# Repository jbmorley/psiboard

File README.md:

# PsiBoard

Psion Series 5 based bluetooth keyboard.

## BOM

### FFC Connector

https://www.digikey.com/en/products/detail/molex/0524372271/3262899

22 Position FFC, FPC Connector Contacts, Bottom 0.020" (0.50mm) Surface Mount, Right Angle

### Reset Switch

https://www.digikey.com/en/products/detail/panasonic-electronic-components/EVQ-P7A01P/4429447

## Development

### Useful Links

- [ZMK Firmware - List of Keycodes](https://zmk.dev/docs/keymaps/list-of-keycodes)
- [ZMK Firmware - Power Management Configuration](https://zmk.dev/docs/config/power)
- [Pro Micro Pinout](https://learn.sparkfun.com/tutorials/pro-micro--fio-v3-hookup-guide/all)

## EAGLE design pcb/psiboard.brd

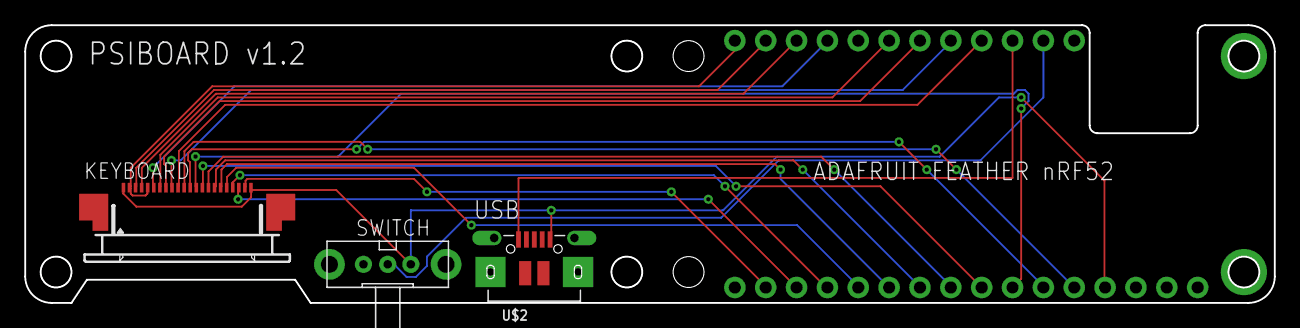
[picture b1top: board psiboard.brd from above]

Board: 2 copper layers, 102.9 x 22.9 mm, 4 parts (1 on the bottom side), 22 nets.

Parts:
FEATHER: FEATHERWING_NODIM; FEATHERWING_DIM
KEYBOARD: 52745-2290
SWITCH: EG1213
U$2: USB_MICRO_PWR; MICROBUILDER_4UCONN_20329

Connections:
2: FEATHER.5, KEYBOARD.11
3: FEATHER.6, KEYBOARD.12
4: FEATHER.7, KEYBOARD.13
5: FEATHER.8, KEYBOARD.14
6: FEATHER.15, KEYBOARD.21
7: FEATHER.23, KEYBOARD.8
8: FEATHER.14, KEYBOARD.20
11: FEATHER.22, KEYBOARD.7
12: FEATHER.11, KEYBOARD.17
13: FEATHER.12, KEYBOARD.18
14: FEATHER.13, KEYBOARD.19
15: FEATHER.24, KEYBOARD.9
16: FEATHER.25, KEYBOARD.10
25: FEATHER.17, KEYBOARD.2, KEYBOARD.5
26: FEATHER.18, KEYBOARD.3
27: FEATHER.19, KEYBOARD.4
28: FEATHER.9, KEYBOARD.15
29: FEATHER.10, KEYBOARD.16
30: FEATHER.20, KEYBOARD.6
EN: FEATHER.27, SWITCH.2
GND: FEATHER.4, KEYBOARD.1, KEYBOARD.22, SWITCH.3, U$2.GND
USB: FEATHER.26, U$2.VBUS

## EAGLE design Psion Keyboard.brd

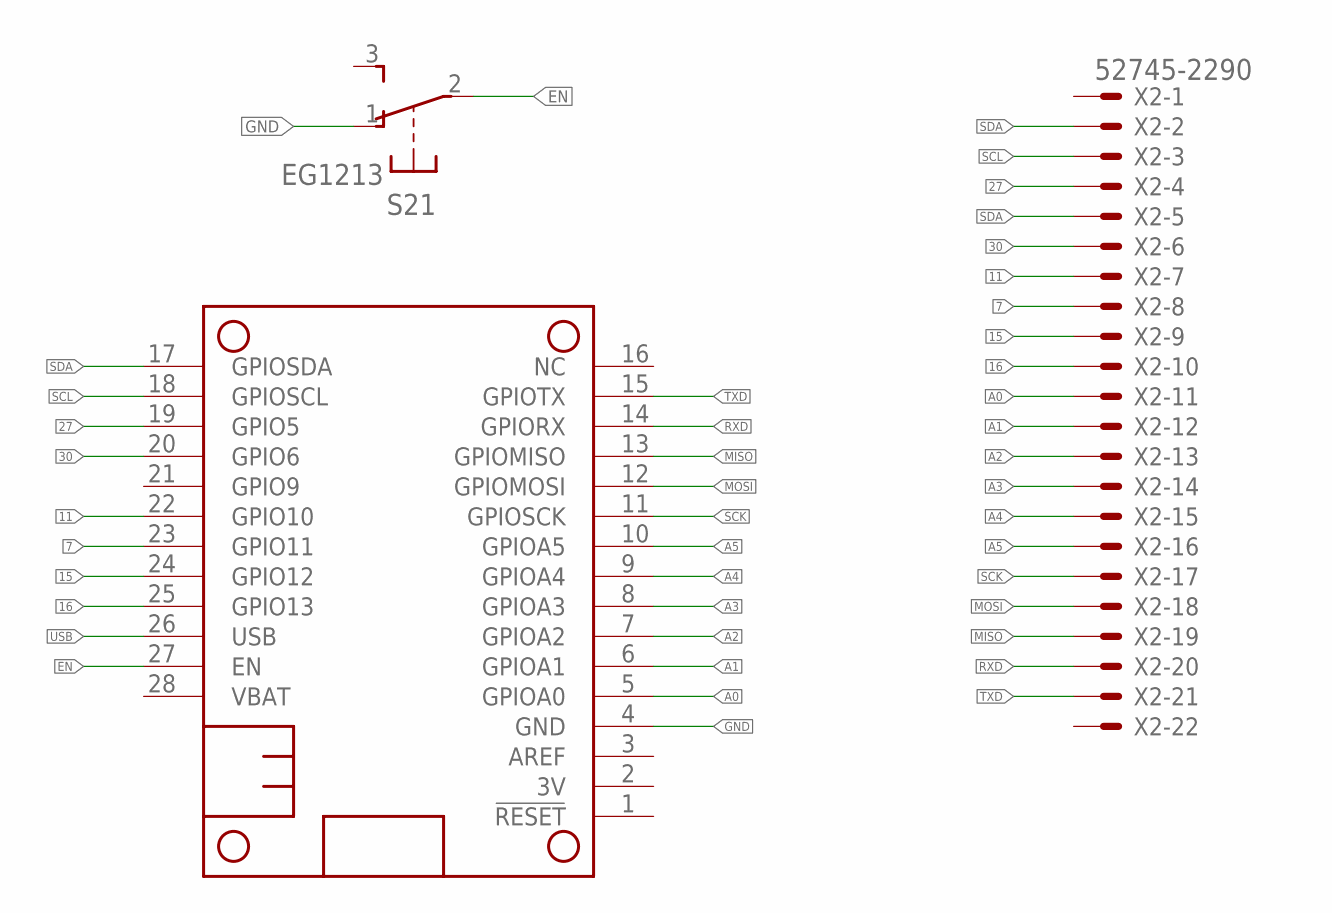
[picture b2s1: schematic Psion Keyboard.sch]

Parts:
MS1: FEATHERWING_NODIM; FEATHERWING_DIM
S2: EG1213
X2: 52745-2290

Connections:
7: MS1.23 (GPIO11), X2.8
11: MS1.22 (GPIO10), X2.7
15: MS1.24 (GPIO12), X2.9
16: MS1.25 (GPIO13), X2.10
27: MS1.19 (GPIO5), X2.4
30: MS1.20 (GPIO6), X2.6
A0: MS1.5 (GPIOA0), X2.11
A1: MS1.6 (GPIOA1), X2.12
A2: MS1.7 (GPIOA2), X2.13
A3: MS1.8 (GPIOA3), X2.14
A4: MS1.9 (GPIOA4), X2.15
A5: MS1.10 (GPIOA5), X2.16
EN: MS1.27 (EN), S2.2
GND: MS1.4 (GND), S2.1 (O)
MISO: MS1.13 (GPIOMISO), X2.19
MOSI: MS1.12 (GPIOMOSI), X2.18
RXD: MS1.14 (GPIORX), X2.20
SCK: MS1.11 (GPIOSCK), X2.17
SCL: MS1.18 (GPIOSCL), X2.3
SDA: MS1.17 (GPIOSDA), X2.2, X2.5
TXD: MS1.15 (GPIOTX), X2.21
USB: MS1.26 (USB)

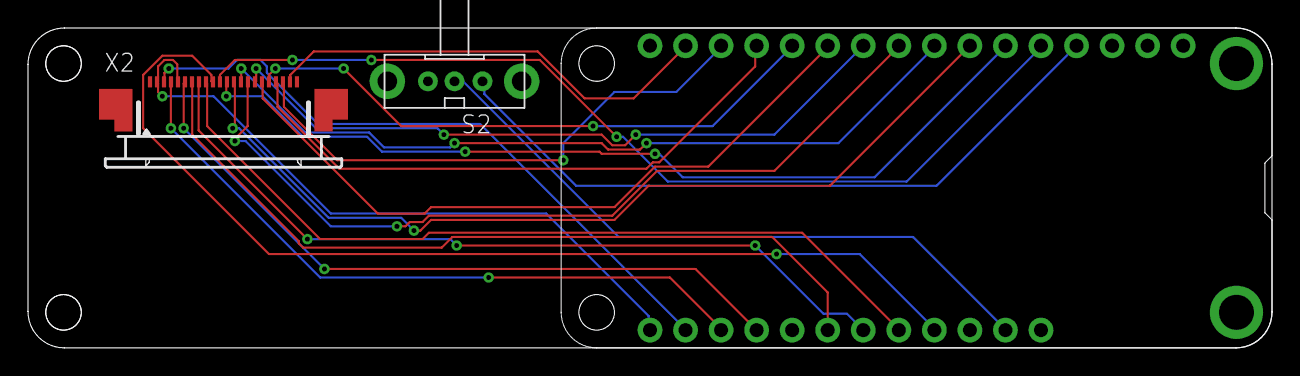
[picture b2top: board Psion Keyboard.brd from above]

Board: 2 copper layers, 88.9 x 22.9 mm, 3 parts (0 on the bottom side), 21 nets.

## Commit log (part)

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2018-02-10 Very first prototype.
    This supports some level of scanning and outputting some key rows.
2018-02-13 General key scanning now works.
2018-02-13 Make keyboard.py executable.
2018-02-14 Fleshing out some of the keys.
2018-02-14 Slightly improved output.
2018-02-14 Storing previous state and emitting key down and key up events.
2018-02-14 Rudimentary shifting support.
2018-02-23 Add the Adafruit hid_keyboard example.
2018-02-23 Some prototype code for interacting with the keyboard.
2018-02-24 Arduino directory structure and lookup table.
2018-02-24 Two columns working.
    Unfortunately this implementation has columns and rows backwards, and should be changed in the future.
2018-02-24 Add some comments.
2018-02-25 Most key events now working.
2018-02-25 Switch over to HID keycodes.
2018-02-25 Rudimentary shifting behaviour and key action.
2018-02-25 Second delay is unnecessary.
2018-02-25 Shift overrides.
2018-02-25 Use KEY_NONE as a re-mappable empty keycode.
2018-02-25 Fn, Menu, and Esc now working.
2018-02-25 Remove one unnecessary row.
2018-02-25 Remove another defunct row.
2018-02-25 Fn key working with the math symbols.
2018-02-25 Fleshing out Fn key behaviour.
2018-02-25 Menu as Command key.
2018-02-28 Cleaner modifier handling.
2018-02-28 Remove unused define.
2018-02-28 Restore the escape key.
    It doesn’t seem to function as I would expect right now.
2018-02-28 Support the control key.
2018-02-28 Using a more appropriate identifier for the Fn key.
2018-02-28 Remove unused variable.
2018-02-28 Update the bluetooth data.
2018-02-28 Slowly cleaning up the code a little.
2018-02-28 Remove the now-legacy serial input support.
2018-03-01 Caps lock.
2018-03-01 More generic modifier event handling.
2018-03-01 Unified modifier handling.
2018-03-02 Switch to using the RX pin (6) instead of DFU for the column.
    This change also required no longer configuring the serial console.
2018-03-04 Initial addition of PCB.
2018-03-04 Basic shape.
2018-03-04 Ignore backup files.
2018-03-04 Add mounting holes.
2018-03-04 Basic board shape.
2018-03-04 Ignore .job files. General shape.
2018-03-04 Add drill holes.
2018-03-05 Rename the firmware file.
2018-03-15 Update eagle version.
2018-03-15 Update pins for the new PCB
    Includes drive-by fix for right shift.
2018-03-15 Disable arrow key modifiers for the time being.
2018-03-25 Initial work on v2 of the PCB.
2018-03-25 Starting to get to the correct board shape.
2018-03-25 Basic board layout now complete, including silkscreen names.
2018-03-25 General board layout improvements.
2018-03-25 General shape now seems correct, as does the silkscreening.
2018-03-25 Schematic is now complete.
2018-03-25 Routing complete.
2018-03-25 Lowercase v for version.
2018-03-25 Remembering to add holes.
2018-03-25 Remove the v1 PCB.
2018-03-25 Add referenced EagleCAD library.
2018-03-25 Add some notes on the changes made to v1.1 of the PCB.
2018-04-07 Add the STL files for the case.
2018-04-07 Update the firmware for the latest PCB.
2018-04-11 Some minor adjustments to the case dimensions
    Includes a first guess at a board mounting height.
2018-04-12 Set up Fusion sync.
2018-07-31 Ignore backup library files.
2018-07-31 Attempting to add a USB-C component.
2018-07-31 Ignore .pro files.
2018-07-31 Remove legacy project file.
2018-07-31 Checking in the first prototype of the USB-C breakout board.
2018-07-31 Add the USB Micro library
2018-07-31 Board design is generally working
2018-07-31 Remove unused USB Micro library.
2018-07-31 Update the board.
2018-07-31 Fix the routing fro the USB.
2018-07-31 Update with Fusion sync.
2018-08-23 Catch the firmware up to PsiBoard v1.2.
2018-09-07 Add images.
2021-02-17 Create LICENSE
2021-02-17 Add an export of the Fusion 360 models.
    The dimensions of these aren't quite right at the moment, but they're intended to help others get started while the project is idle.
2024-05-26 Add more ideas and sketches
2025-10-06 Add the keyboard membrane reference scans
2025-10-06 Move the PCB into the v1 directory
2025-10-06 Update the hero image
2025-10-06 Move reference sketches
2025-10-07 Remove legacy breakout board
2025-10-07 Remove proof-of-concept Raspberry Pi polling scripts
2025-10-07 Move the legacy Fusion 360 case designs into `v1`
2025-10-07 Move the legacy STL exports into the v1 folder
2025-10-07 Remove legacy tasks from the readme
2025-10-07 Move the legacy firmware into the `v1` directory
2025-10-07 Move the legacy Eagle component libraries into `v1/pcb`
2025-10-07 Add the nice!nano version of the PCB
2025-10-07 Remove unnecessary files
2025-10-07 Remove exported step file
2025-10-07 Rename the pcb project
2025-10-07 Update gitignore
2025-10-07 Add the nice!nano version of the PCB (#2)
2025-10-07 Add the ZMK firmware
2025-10-07 Rename the firmware directory
2025-10-07 Add the ZMK firmware (#3)
2025-10-07 Rename the workflow file
2025-10-07 Rename the workflow file (#4)
2025-10-07 Reanme the workflow and firmware build job
2025-10-07 docs: Add a GitHub Actions workflow status badge
2025-10-07 docs: Add a GitHub Actions workflow status badge (#6)
2025-10-07 Rename the workflow and firmware build job (#5)
2025-10-07 docs: Add a full stop after the description
2025-10-07 docs: Add a full stop after the description (#7)
2025-10-11 fix: Remove unnecessary NC scanning row
2025-10-11 Switch rows 1 and 2 to test things
2025-10-11 Change the delays
2025-10-11 Switch the columns this time and see if thigns move
2025-10-11 Active low instead?
2025-10-11 Go back to the original layout
2025-10-12 Simplify things
2025-10-12 fix(firmware): Remove unnecessary scanning row (#8)
2025-10-12 Hand-route keyboard to simplify layout
2025-10-12 Latest iteration
2025-10-12 Add components to readme
2025-10-12 Add ground plane
2025-10-12 Ignore auto-generated archives
2025-10-14 Update the firmware to match the new PCB layout
2025-10-14 Increase the PCB size to leave room for a status LED
2025-10-14 Final versions
2025-10-14 fix(pcb): Hand-route keyboard to simplify layout (#9)
    This change also introduces a ground plane and makes the PCB
    significantly larger to allow placement of a status LED in future
    iterations.
2025-10-14 chore(pcb): Ignore autosave files
2025-10-14 chore(pcb): Ignore autosave files (#10)
2025-10-25 chore: Add nice!nano reference model and pinout
2025-10-26 chore: Add nice!nano reference model and pinout (#11)
2025-10-26 feat: Add the first-cut manufacturing exports
2025-10-26 feat: Add the first-cut manufacturing exports (#12)
2025-11-08 fix(firmware): Update the wakeup source pinout
2025-12-02 docs: Add some useful references to the readme
    Added development section with useful links.
2025-12-02 docs: Add some useful references to the readme (#20)
    Added development section with useful links.
